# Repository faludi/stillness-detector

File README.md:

The Stillness Detector senses presence and motion to determine if there is a person standing in front of it and whether that person is currently standing still. It is intended to provide a trigger to interactive art pieces that require stillness rather than action from the viewer. 

See the [DOCUMENTATION](DOCUMENTATION.md) for more information.

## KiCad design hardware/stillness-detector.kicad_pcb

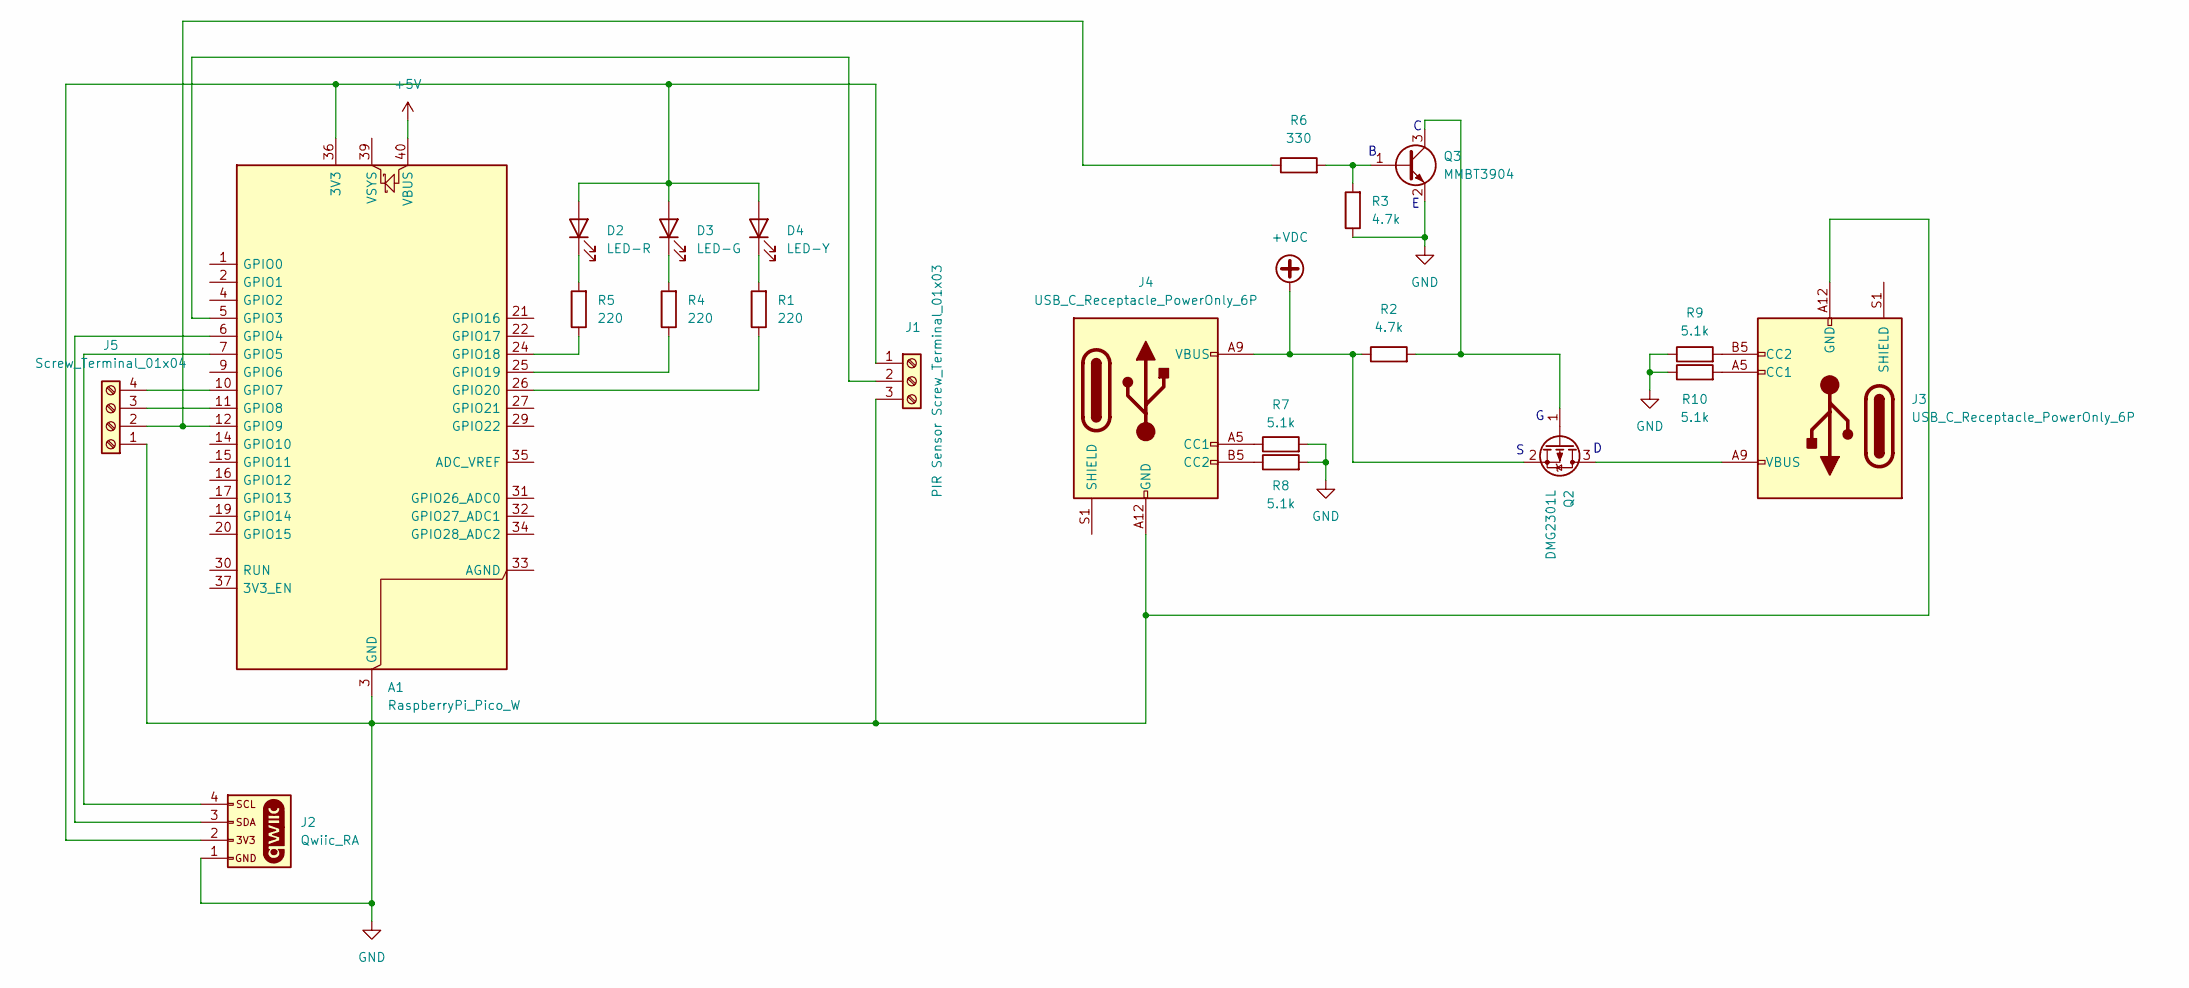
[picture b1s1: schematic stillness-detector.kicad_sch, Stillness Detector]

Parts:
A1: RaspberryPi_Pico_W; RaspberryPi_Pico_Common_Unspecified
D2: LED-R; LED_1206_3216Metric
D3: LED-G; LED_1206_3216Metric
D4: LED-Y; LED_1206_3216Metric
J1: PIR Sensor Screw_Terminal_01x03; TerminalBlock_Xinya_XY308-2.54-3P_1x03_P2.54mm_Horizontal
J2: Qwiic_RA; JST_1x04_P1.0mm_Horizontal_SMD
J3, J4: USB_C_Receptacle_PowerOnly_6P; USB_C_Receptacle_GCT_USB4125-xx-x-0190_6P_TopMnt_Horizontal
J5: Screw_Terminal_01x04; TerminalBlock_Xinya_XY308-2.54-4P_1x04_P2.54mm_Horizontal
Q2: DMG2301L; SOT-23
Q3: MMBT3904; SOT-23
R1, R4, R5: 220; R_1206_3216Metric
R2, R3: 4.7k; R_1210_3225Metric_Pad1.30x2.65mm_HandSolder
R6: 330; R_1210_3225Metric_Pad1.30x2.65mm_HandSolder
R7, R8, R9, R10: 5.1k; R_1210_3225Metric_Pad1.30x2.65mm_HandSolder

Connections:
+5V: A1.40 (VBUS)
+VDC: J4.A9 (VBUS), J4.B9 (VBUS), Q2.2 (S), R2.1
GND: A1.3 (GND), A1.8 (GND), A1.13 (GND), A1.18 (GND), A1.23 (GND), A1.28 (GND), A1.38 (GND), J1.3, J2.1, J3.A12 (GND), J3.B12 (GND), J4.A12 (GND), J4.B12 (GND), J5.1, Q3.2 (E), R3.1, R7.2, R8.2, R9.1, R10.1
unnamed: A1.36 (3V3), D2.2 (A), D3.2 (A), D4.2 (A), J1.1, J2.2
unnamed: A1.5 (GPIO3), J1.2
unnamed: A1.6 (GPIO4), J2.3
unnamed: A1.7 (GPIO5), J2.4
unnamed: A1.10 (GPIO7), J5.4
unnamed: A1.11 (GPIO8), J5.3
unnamed: A1.12 (GPIO9), J5.2, R6.1
unnamed: A1.24 (GPIO18), R5.1
unnamed: A1.25 (GPIO19), R4.1
unnamed: A1.26 (GPIO20), R1.1
unnamed: D2.1 (K), R5.2
unnamed: D3.1 (K), R4.2
unnamed: D4.1 (K), R1.2
unnamed: J3.A5 (CC1), R10.2
unnamed: J3.B5 (CC2), R9.2
unnamed: J4.A5 (CC1), R7.1
unnamed: J4.B5 (CC2), R8.1
unnamed: J3.A9 (VBUS), J3.B9 (VBUS), Q2.3 (D)
unnamed: Q2.1 (G), Q3.3 (C), R2.2
unnamed: Q3.1 (B), R3.2, R6.2

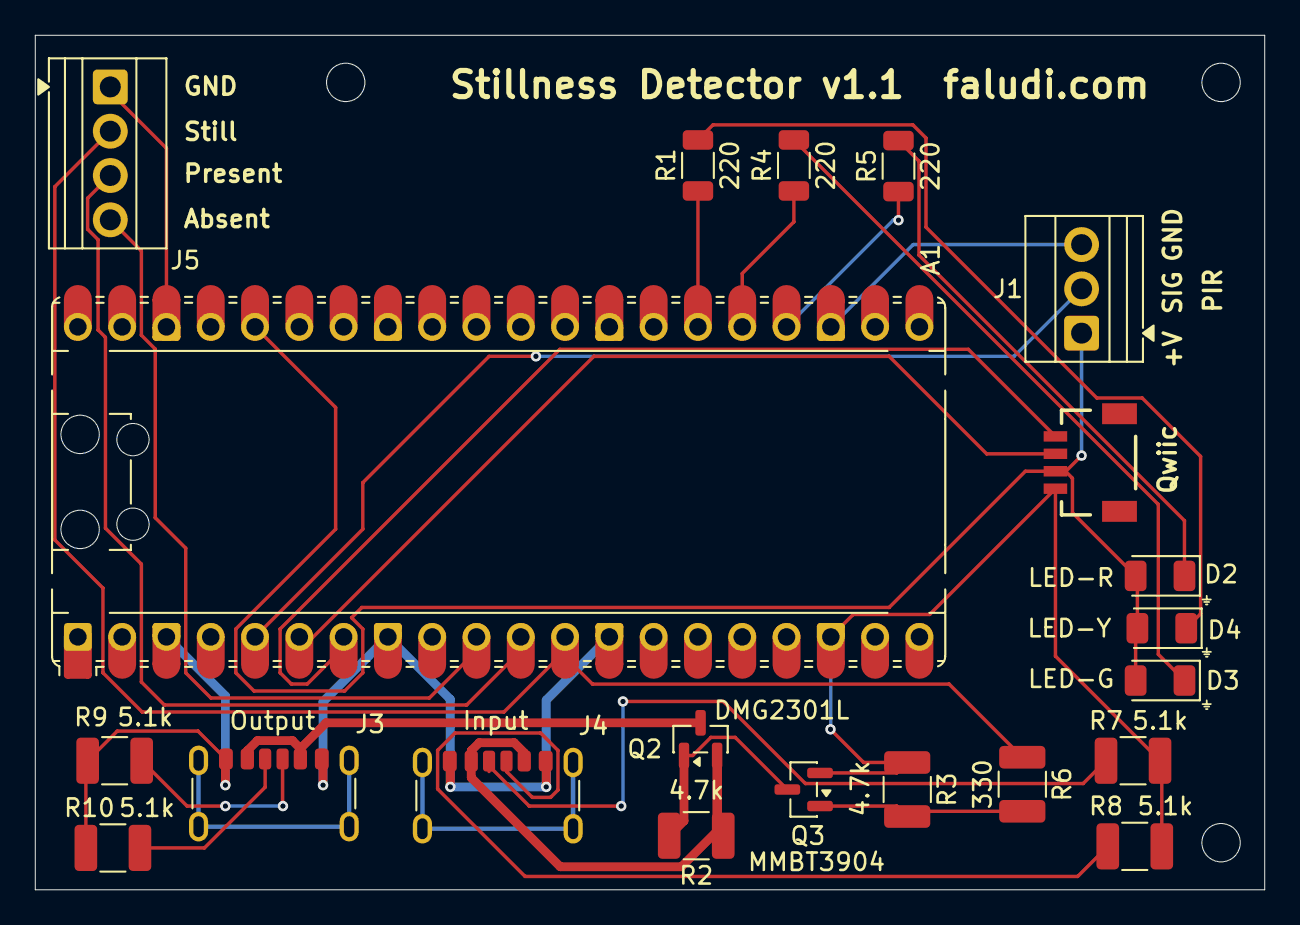
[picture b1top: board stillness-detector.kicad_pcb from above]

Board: 2 copper layers, 70.5 x 49.0 mm, 21 parts (0 on the bottom side), 22 nets.

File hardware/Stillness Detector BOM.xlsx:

Id | Designator | Footprint | Quantity | Q x 10 | Designation | Cost | Extended Cost |  | Supplier and ref
1 | J3,J4 | USB_C_Receptacle_GCT_USB4125-xx-x-0190_6P_TopMnt_Horizontal | 2 | 20 | USB_C_PowerOnly | 0.6 | 1.2 | Digi-Key | 2073-USB4125-GF-A-0190CT-ND
2 | Q3 | SOT-23 | 1 | 10 | MMBT3904 | 7.0000000000000007E-2 | 7.0000000000000007E-2 | Digi-Key | 4878-MMBT3904CT-ND
 | R7-10 | R_1210_3225Metric_Pad1.30x2.65mm_HandSolder | 4 | 40 | 5.1k | 4.7E-2 | 0.188 | Digi-Key | 311-5.10KFRCT-ND
3 | R6 | R_1210_3225Metric_Pad1.30x2.65mm_HandSolder | 1 | 10 | 330 | 1.0999999999999999E-2 | 1.0999999999999999E-2 | Digi-Key | 311-330FRCT-ND
4 | R5,R4,R1 | R_1206_3216Metric | 3 | 30 | 220 | 0.01 | 0.03 | Digi-Key | 311-220FRCT-ND
5 | R3,R2 | R_1210_3225Metric_Pad1.30x2.65mm_HandSolder | 2 | 20 | 4.7k | 1.0800000000000001E-2 | 2.1600000000000001E-2 | Digi-Key | 311-4.70KFRCT-ND
6 | Q2 | SOT-23 | 1 | 10 | DMG2301L | 0.161 | 0.161 | Digi-Key | DMG2301L-7DICT-ND
7 | J5 | TerminalBlock_Xinya_XY308-2.54-4P_1x04_P2.54mm_Horizontal | 1 | 10 | Screw_Terminal_01x04 | 1.63 | 1.63 | Digi-Key | ED10563-ND
8 | J2 | JST_1x04_P1.0mm_Horizontal_SMD | 1 | 10 | Qwiic_RA | 0.42399999999999999 | 0.42399999999999999 | Digi-Key | 455-SM04B-SRSS-TBCT-ND
9 | J1 | TerminalBlock_Xinya_XY308-2.54-3P_1x03_P2.54mm_Horizontal | 1 | 10 | PIR Sensor Screw_Terminal_01x03 | 1.26 | 1.26 | Digi-Key | ED10562-ND
10 | D4 | LED_1206_3216Metric | 1 | 10 | LED-Y | 0.125 | 0.125 | Digi-Key | 160-1406-1-ND
11 | D3 | LED_1206_3216Metric | 1 | 10 | LED-G | 9.0999999999999998E-2 | 9.0999999999999998E-2 | Digi-Key | 160-1456-1-ND
12 | D2 | LED_1206_3216Metric | 1 | 10 | LED-R | 9.0999999999999998E-2 | 9.0999999999999998E-2 | Digi-Key | 160-1168-1-ND
13 | A1 | RaspberryPi_Pico_Common_Unspecified | 1 | 10 | Raspberry Pi Pico 2 WH | 8 | 8 | Digi-Key | 2648-SC1634-ND
 |  | Female headers 20-pin for Pico | 2 | 20 | 20-position Female header | 0.85 | 1.7 | Digi-Key | 21601X20GSE
 |  | PIR Sensor | 1 | 10 | SR602 PIR | 1.996 | 1.996 | Amazon | B096NZ4P3K
 |  | TOF Sensor | 1 | 10 | ACEIRMC TOF400C | 5.4725000000000001 | 5.4725000000000001 | Amazon | B0FQ4ZXRZS
 |  | PIR cables | 3 | 30 | F - M | 0.12475 | 0.37424999999999997 | Digi-Key | 1528-1161-ND
 |  | TOF cables | 4 | 40 | F - M | 0.12475 | 0.499 | Digi-Key | 1528-1161-ND
 |  | PCB | 1 | 10 |  | 16.05 | 16.05 | OSH Park | https://oshpark.com/shared_projects/h9REVbJo
 |  |  |  |  |  |  | 39.394350000000003

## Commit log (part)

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2026-01-18 initial version
2026-01-19 replace ultrasonic sensing with tof
2026-01-22 add stillness detector class, RGB leds, delays
2026-01-24 damping of occasional motion
2026-01-24 improvements to timings
2026-01-26 min and max distance
2026-01-26 add allowable distance change
2026-01-28 Refine stillness detection logic and add get calls to StillnessDetector class
2026-01-30 change settling delay concept and add modes for easier configuration
2026-01-30 replace None test in update()
2026-01-30 add settings and reset function if TOF fails
2026-03-06 add three outputs for intergration with artwork
2026-03-10 Improvements to PIR stability with pulldown and new damping logic
2026-03-11 Add diagrams and BOM to readme
2026-03-11 better header text
2026-03-11 Improve detection and change out a BOM part
2026-03-12 Update readme with pinouts and settings.
2026-03-21 Change common cathode to common annode RGY LED.
2026-05-15 bugfixes and reversion to LED sink
2026-05-19 update PIR settings
2026-05-24 add hardware assets
2026-05-31 First draft of documentation
2026-06-03 Update docs
2026-06-03 More docs updates
2026-06-05 Remove old information from README
2026-06-05 testing an image
2026-06-05 add directory
2026-06-05 add images to docs
2026-06-05 image sizes test
2026-06-05 image test
2026-06-05 images to grid
2026-06-05 adjust image sizes
2026-06-05 back to single column of images
2026-06-05 Add images to instructions
2026-06-18 adjust image size
2026-06-18 start with self.elapsed_time = 0 instead of None
